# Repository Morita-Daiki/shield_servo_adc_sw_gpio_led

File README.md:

# shield_solenoid

[回路図](shield_servo_adc_sw_gpio_led.pdf)

[GBR](GBRsole/shield_sole.zip)

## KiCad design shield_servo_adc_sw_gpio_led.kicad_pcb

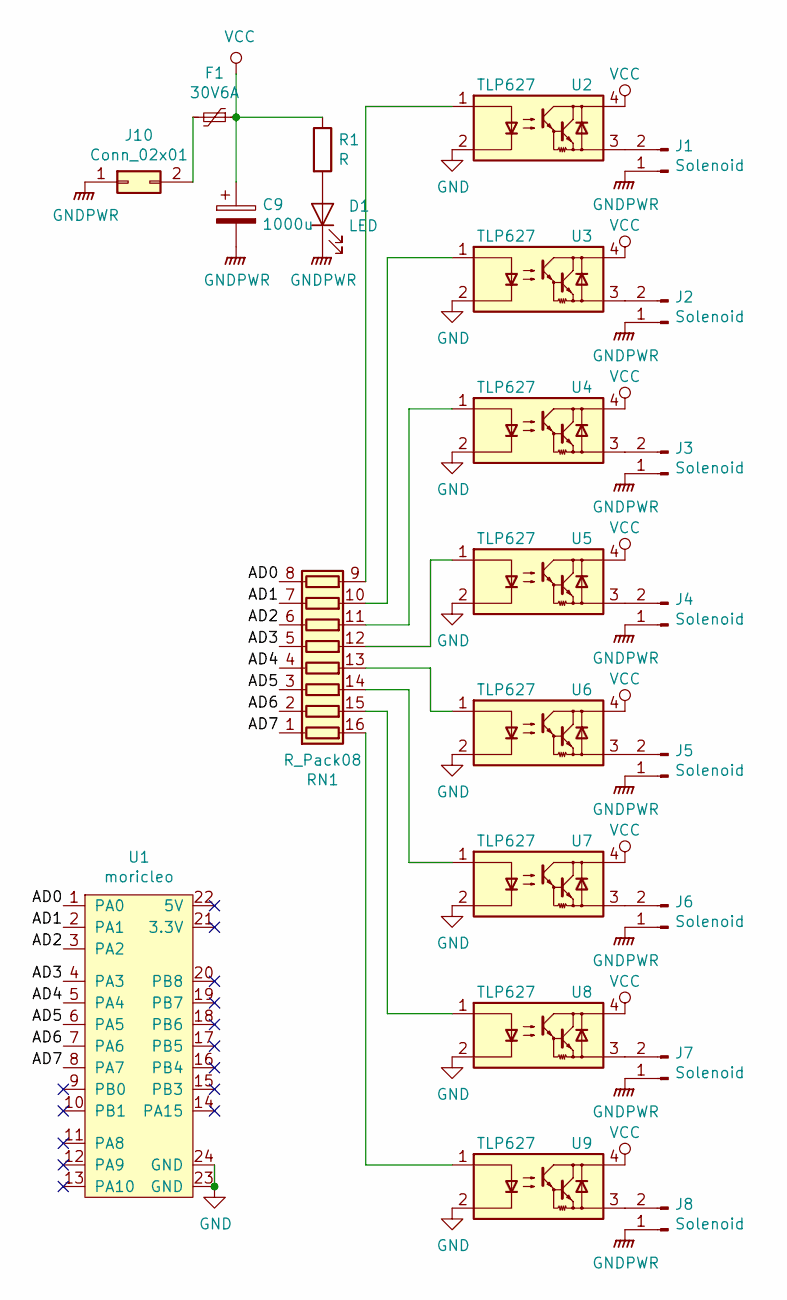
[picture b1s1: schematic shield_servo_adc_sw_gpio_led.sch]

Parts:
C9: 1000u; CP_Radial_D10.0mm_P5.00mm_P7.50mm
D1: LED; LED_0603_1608Metric
F1: 30V6A; Fuse_Bourns_MF-RHT600
J1, J2, J3, J4, J5, J6, J7, J8: Solenoid; JST_PH_S2B-PH-K_1x02_P2.00mm_Horizontal
J10: Conn_02x01; AMASS_XT30PW-M_1x02_P2.50mm_Horizontal
R1: R; R_0603_1608Metric
RN1: R_Pack08; R_Array_Convex_8x0602
U1: moricleo
U2, U3, U4, U5, U6, U7, U8, U9: TLP627; DIP-4_W7.62mm

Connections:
/AD0: RN1.8 (R8.1), U1.1 (PA0)
/AD1: RN1.7 (R7.1), U1.2 (PA1)
/AD2: RN1.6 (R6.1), U1.3 (PA2)
/AD3: RN1.5 (R5.1), U1.4 (PA3)
/AD4: RN1.4 (R4.1), U1.5 (PA4)
/AD5: RN1.3 (R3.1), U1.6 (PA5)
/AD6: RN1.2 (R2.1), U1.7 (PA6)
/AD7: RN1.1 (R1.1), U1.8 (PA7)
GND: U1.23 (GND), U1.24 (GND), U2.2, U3.2, U4.2, U5.2, U6.2, U7.2, U8.2, U9.2
GNDPWR: C9.2, D1.1 (K), J1.1, J2.1, J3.1, J4.1, J5.1, J6.1, J7.1, J8.1, J10.1
unnamed: D1.2 (A), R1.2
unnamed: F1.2, J10.2
unnamed: J1.2, U2.3
unnamed: J2.2, U3.3
unnamed: J3.2, U4.3
unnamed: J4.2, U5.3
unnamed: J5.2, U6.3
unnamed: J6.2, U7.3
unnamed: J7.2, U8.3
unnamed: J8.2, U9.3
unnamed: RN1.9 (R8.2), U2.1
unnamed: RN1.10 (R7.2), U3.1
unnamed: RN1.11 (R6.2), U4.1
unnamed: RN1.12 (R5.2), U5.1
unnamed: RN1.13 (R4.2), U6.1
unnamed: RN1.14 (R3.2), U7.1
unnamed: RN1.15 (R2.2), U8.1
unnamed: RN1.16 (R1.2), U9.1
VCC: C9.1, F1.1, R1.1, U2.4, U3.4, U4.4, U5.4, U6.4, U7.4, U8.4, U9.4

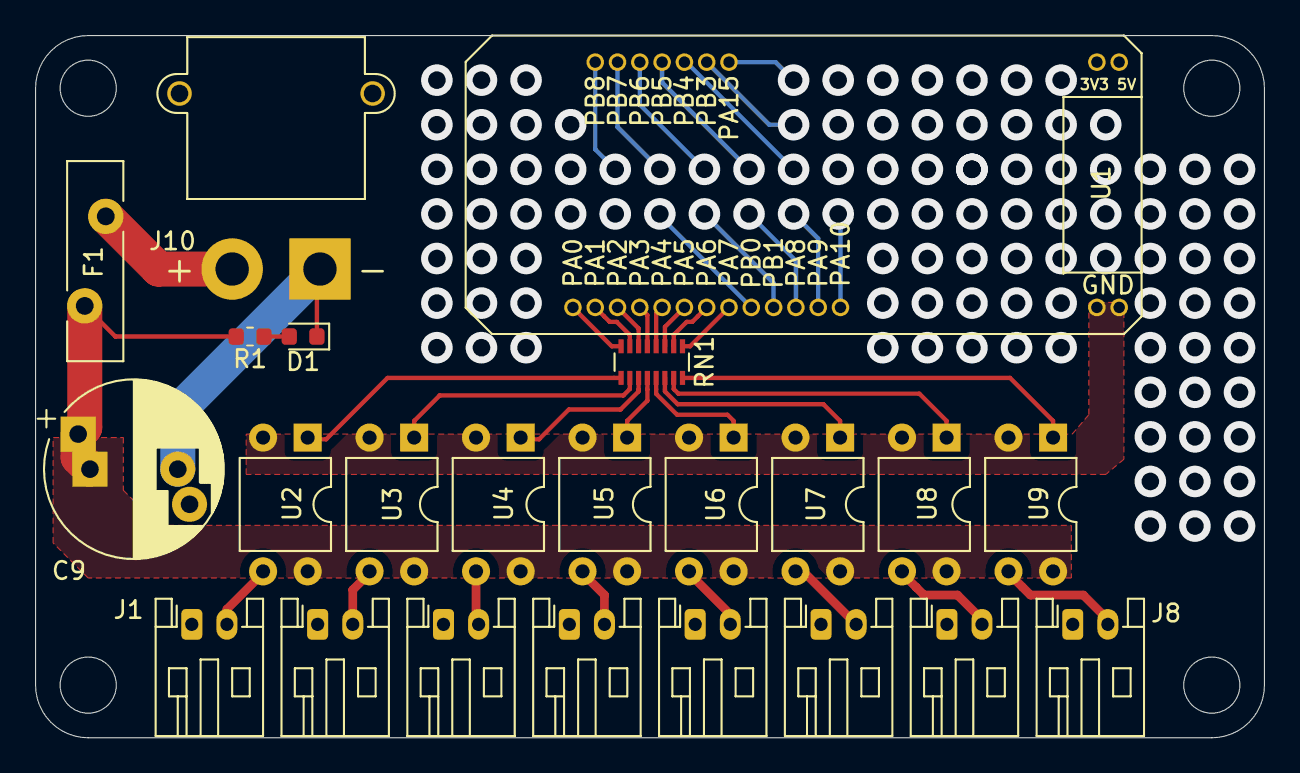
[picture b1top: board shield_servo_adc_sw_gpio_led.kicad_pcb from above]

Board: 2 copper layers, 70.0 x 40.0 mm, 23 parts (0 on the bottom side), 29 nets.

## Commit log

2020-11-14 tlp627
2020-11-14 solenoid 完成
2020-11-14 create pdf
2020-11-14 make gbr
2020-11-14 name change
